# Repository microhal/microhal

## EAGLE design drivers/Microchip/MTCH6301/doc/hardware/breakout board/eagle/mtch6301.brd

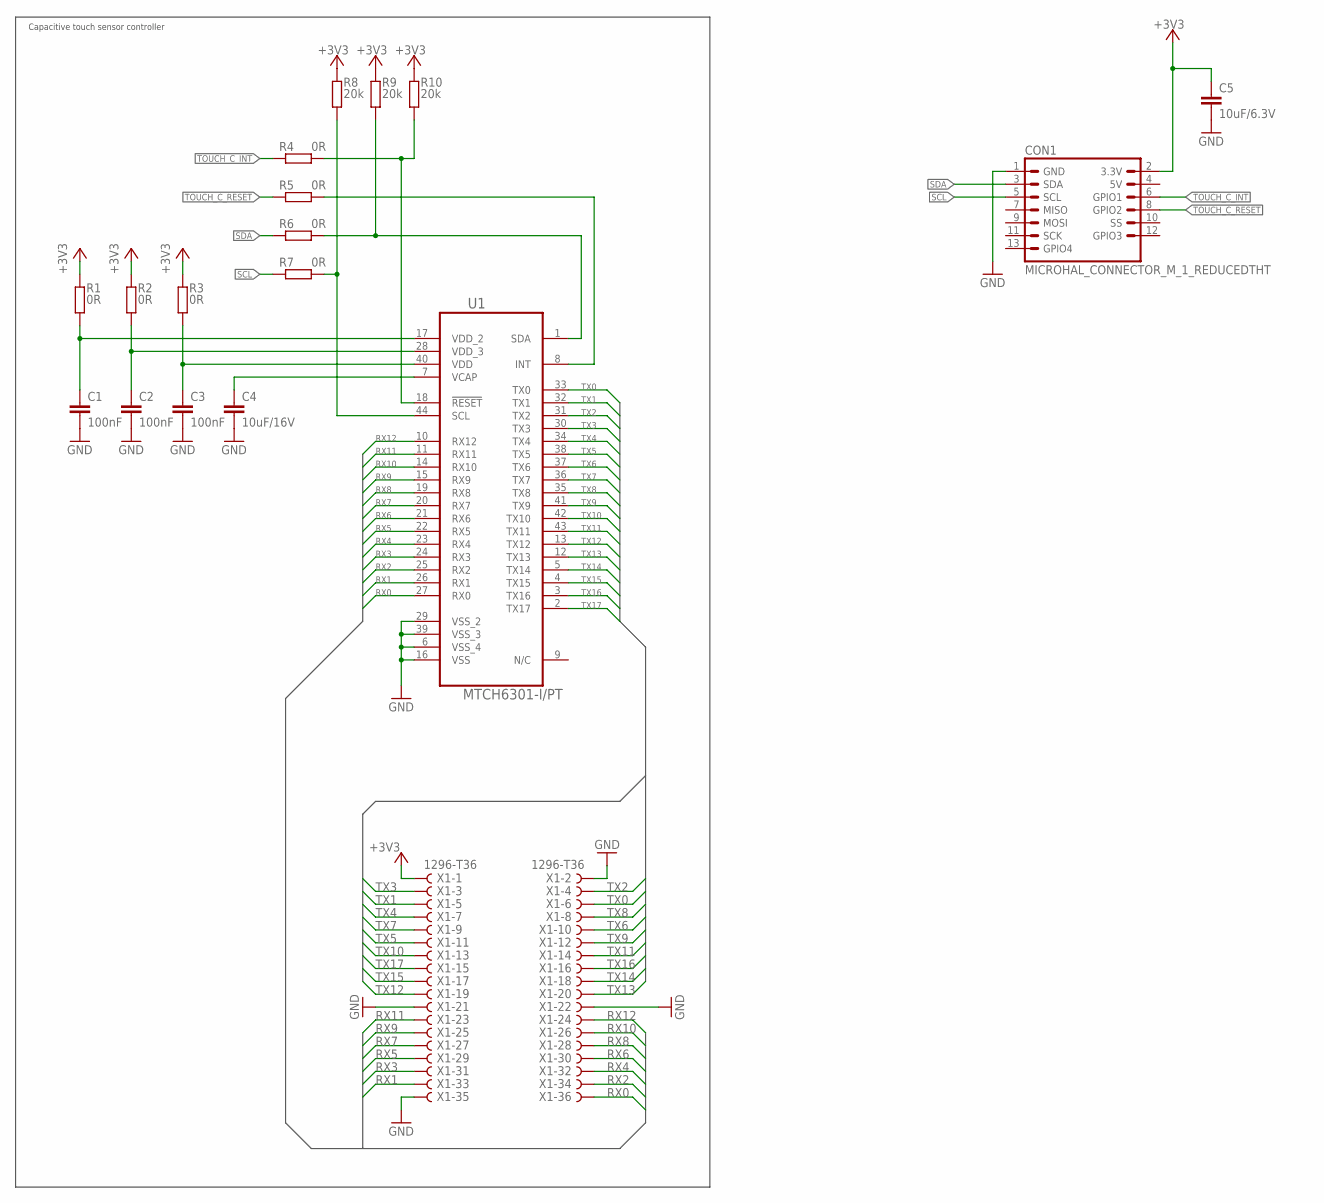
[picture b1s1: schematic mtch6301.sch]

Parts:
C1, C2, C3: 100nF; C0603K
C4: 10uF/16V; C1206K
C5: 10uF/6.3V; C0805K
CON1: MICROHAL_CONNECTOR_M_1_REDUCEDTHT; MA07-2
R1, R2, R3, R4, R5, R6, R7: 0R; R0603
R8, R9, R10: 20k; R0603
U1: MTCH6301-I/PT; TQFP80P1200X1200X120-44N
X1: 1296-T36; 1296-36

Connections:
+3V3: C5.1, CON1.2 (3.3V), R1.1, R2.1, R3.1, R8.1, R9.1, R10.1, X1.1
GND: C1.2, C2.2, C3.2, C4.2, C5.2, CON1.1 (GND), U1.6 (VSS_4), U1.16 (VSS), U1.29 (VSS_2), U1.39 (VSS_3), X1.2, X1.21, X1.22, X1.35
unnamed: C4.1, U1.7 (VCAP)
unnamed: C3.1, R3.2, U1.40 (VDD)
unnamed: C2.1, R2.2, U1.28 (VDD_3)
unnamed: C1.1, R1.2, U1.17 (VDD_2)
unnamed: R7.1, R8.2, U1.44 (SCL)
unnamed: R4.1, R10.2, U1.18 (!RESET)
unnamed: R6.1, R9.2, U1.1 (SDA)
unnamed: R5.1, U1.8 (INT)
RX0: U1.27 (RX0), X1.36
RX1: U1.26 (RX1), X1.33
RX2: U1.25 (RX2), X1.34
RX3: U1.24 (RX3), X1.31
RX4: U1.23 (RX4), X1.32
RX5: U1.22 (RX5), X1.29
RX6: U1.21 (RX6), X1.30
RX7: U1.20 (RX7), X1.27
RX8: U1.19 (RX8), X1.28
RX9: U1.15 (RX9), X1.25
RX10: U1.14 (RX10), X1.26
RX11: U1.11 (RX11), X1.23
RX12: U1.10 (RX12), X1.24
SCL: CON1.5 (SCL), R7.2
SDA: CON1.3 (SDA), R6.2
TOUCH_C_INT: CON1.6 (GPIO1), R4.2
TOUCH_C_RESET: CON1.8 (GPIO2), R5.2
TX0: U1.33 (TX0), X1.6
TX1: U1.32 (TX1), X1.5
TX2: U1.31 (TX2), X1.4
TX3: U1.30 (TX3), X1.3
TX4: U1.34 (TX4), X1.7
TX5: U1.38 (TX5), X1.11
TX6: U1.37 (TX6), X1.10
TX7: U1.36 (TX7), X1.9
TX8: U1.35 (TX8), X1.8
TX9: U1.41 (TX9), X1.12
TX10: U1.42 (TX10), X1.13
TX11: U1.43 (TX11), X1.14
TX12: U1.13 (TX12), X1.19
TX13: U1.12 (TX13), X1.20
TX14: U1.5 (TX14), X1.18
TX15: U1.4 (TX15), X1.17
TX16: U1.3 (TX16), X1.16
TX17: U1.2 (TX17), X1.15

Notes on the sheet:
Capacitive touch sensor controller

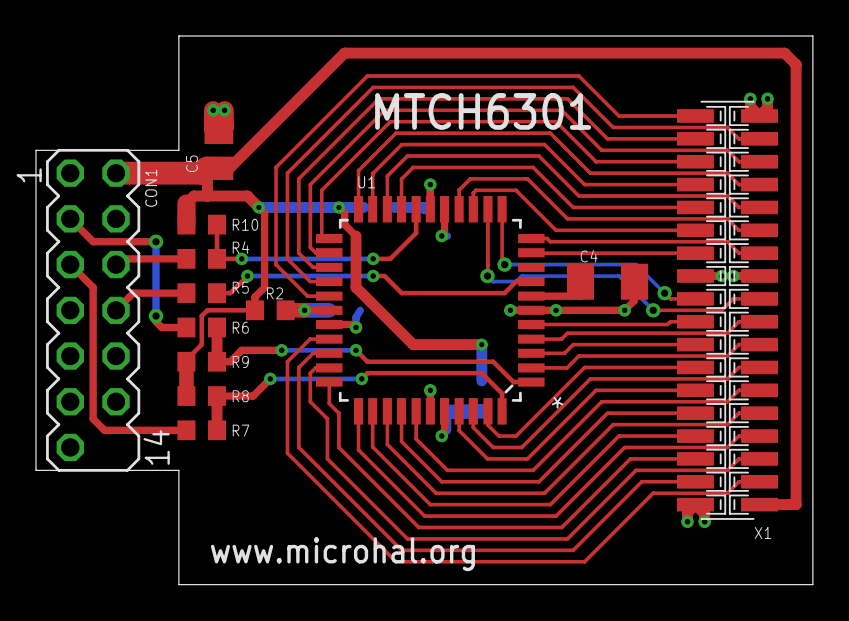
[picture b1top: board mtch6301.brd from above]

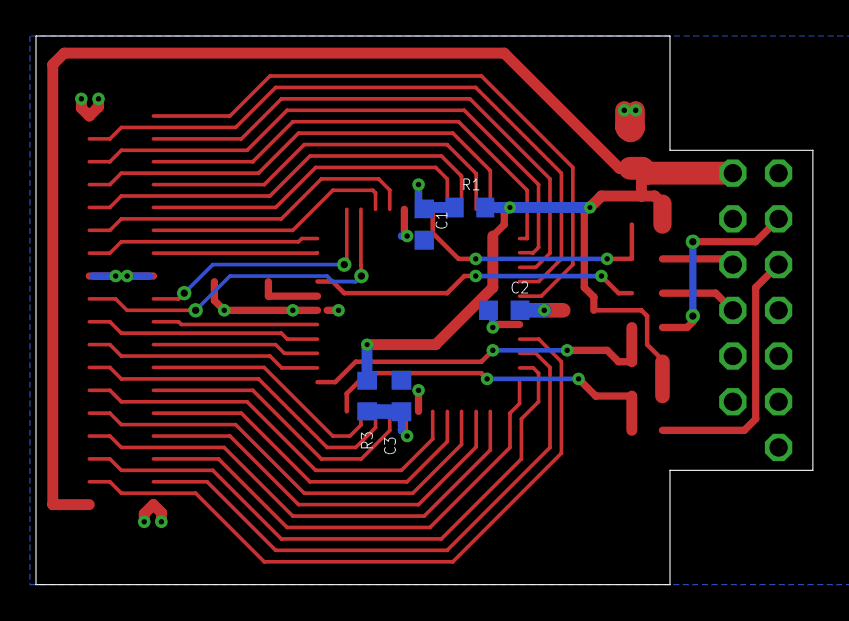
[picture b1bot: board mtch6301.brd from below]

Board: 2 copper layers, 43.2 x 30.5 mm, 18 parts (5 on the bottom side), 45 nets.

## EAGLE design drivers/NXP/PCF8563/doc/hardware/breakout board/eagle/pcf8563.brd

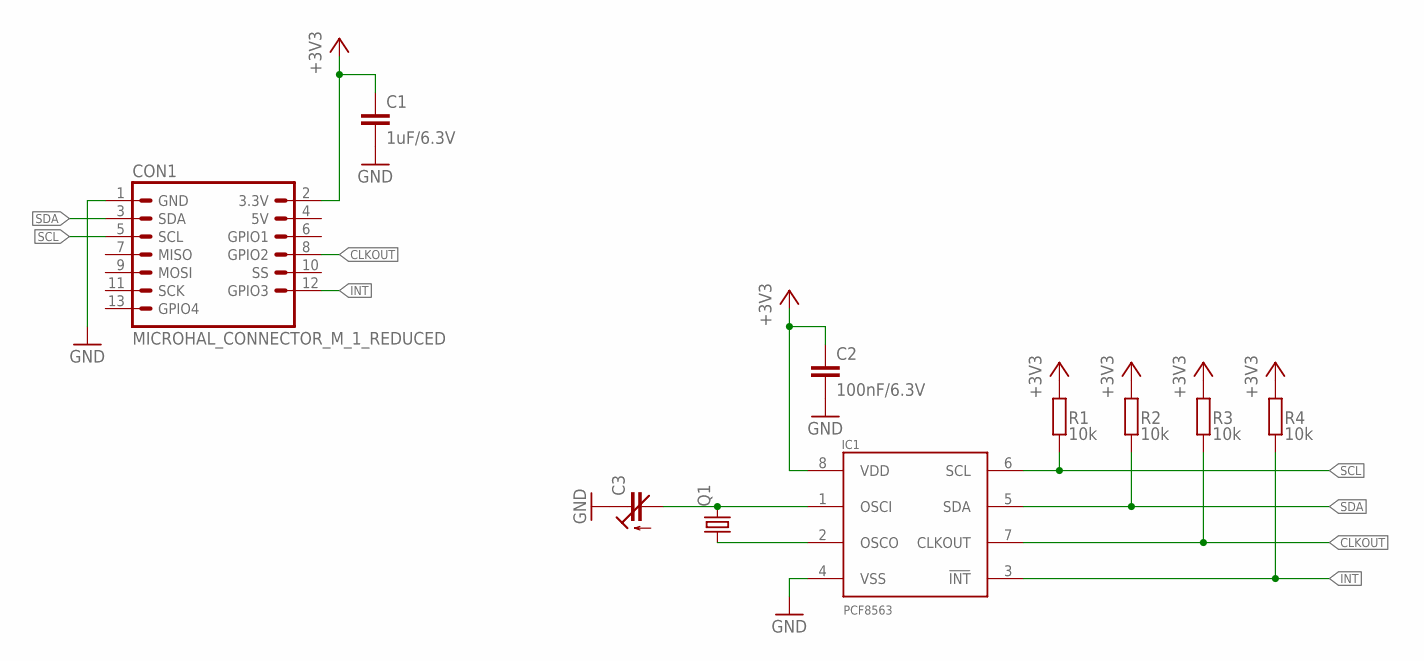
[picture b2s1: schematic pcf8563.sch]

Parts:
C1: 1uF/6.3V; C0805K
C2: 100nF/6.3V; C0603K
C3: C-TRIMMTZBX4; CTRIMTZBX4
CON1: MICROHAL_CONNECTOR_M_1_REDUCED; MICROHAL_CONNECTOR_M_1_REDUCED_EDGE
IC1: PCF8563; SO08
Q1: CRYSTALTC38H; TC38H
R1, R2, R3, R4: 10k; R0603

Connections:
+3V3: C1.1, C2.1, CON1.2 (3.3V), IC1.8 (VDD), R1.2, R2.2, R3.2, R4.2
CLKOUT: CON1.8 (GPIO2), IC1.7 (CLKOUT), R3.1
GND: C1.2, C2.2, C3.1 (E), CON1.1 (GND), IC1.4 (VSS)
INT: CON1.12 (GPIO3), IC1.3 (!INT), R4.1
unnamed: C3.2 (A), IC1.1 (OSCI), Q1.2
unnamed: IC1.2 (OSCO), Q1.1
SCL: CON1.5 (SCL), IC1.6 (SCL), R1.1
SDA: CON1.3 (SDA), IC1.5 (SDA), R2.1

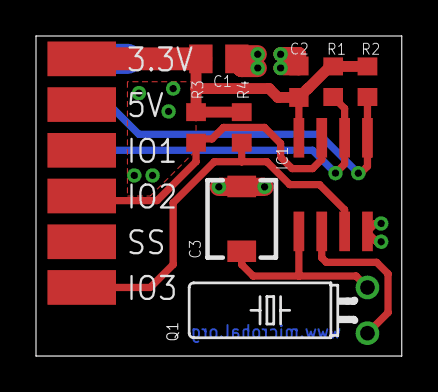
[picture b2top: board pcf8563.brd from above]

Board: 2 copper layers, 20.3 x 17.8 mm, 10 parts (0 on the bottom side), 8 nets.

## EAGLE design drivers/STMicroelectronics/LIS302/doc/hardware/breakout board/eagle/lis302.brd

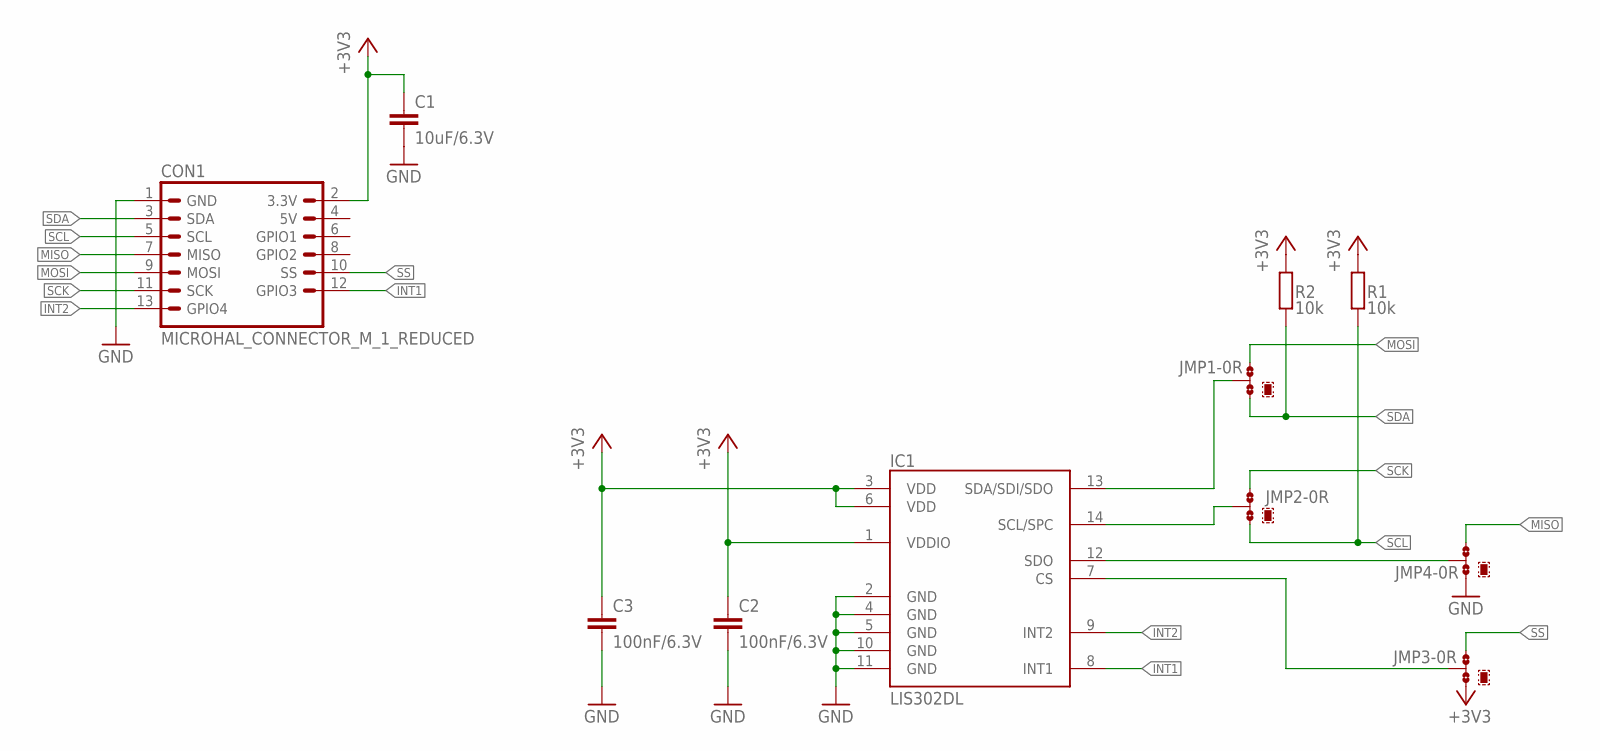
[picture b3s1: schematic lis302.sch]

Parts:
C1: 10uF/6.3V; C0805K
C2, C3: 100nF/6.3V; C0603K
CON1: MICROHAL_CONNECTOR_M_1_REDUCED; MICROHAL_CONNECTOR_M_1_REDUCED_EDGE
IC1: LIS302DL; LGA14
JMP1, JMP2, JMP3, JMP4: 0R-JUMPC; C0R-JMP
R1, R2: 10k; R0603

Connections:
+3V3: C1.1, C2.1, C3.1, CON1.2 (3.3V), IC1.1 (VDDIO), IC1.3 (VDD), IC1.6 (VDD), JMP3.1, R1.2, R2.2
GND: C1.2, C2.2, C3.2, CON1.1 (GND), IC1.2 (GND), IC1.4 (GND), IC1.5 (GND), IC1.10 (GND), IC1.11 (GND), JMP4.1
INT1: CON1.12 (GPIO3), IC1.8 (INT1)
INT2: CON1.13 (GPIO4), IC1.9 (INT2)
MISO: CON1.7 (MISO), JMP4.3
MOSI: CON1.9 (MOSI), JMP1.3
unnamed: IC1.13 (SDA/SDI/SDO), JMP1.2
unnamed: IC1.14 (SCL/SPC), JMP2.2
unnamed: IC1.12 (SDO), JMP4.2
unnamed: IC1.7 (CS), JMP3.2
SCK: CON1.11 (SCK), JMP2.3
SCL: CON1.5 (SCL), JMP2.1, R1.1
SDA: CON1.3 (SDA), JMP1.1, R2.1
SS: CON1.10 (SS), JMP3.3

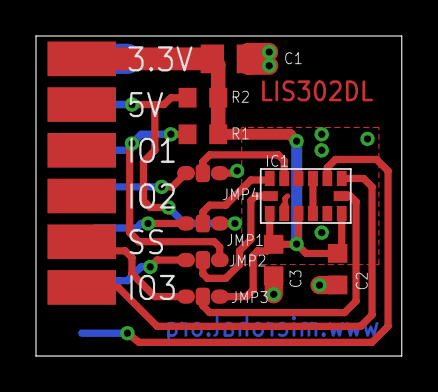
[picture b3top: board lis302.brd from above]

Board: 2 copper layers, 20.3 x 17.8 mm, 11 parts (0 on the bottom side), 14 nets.

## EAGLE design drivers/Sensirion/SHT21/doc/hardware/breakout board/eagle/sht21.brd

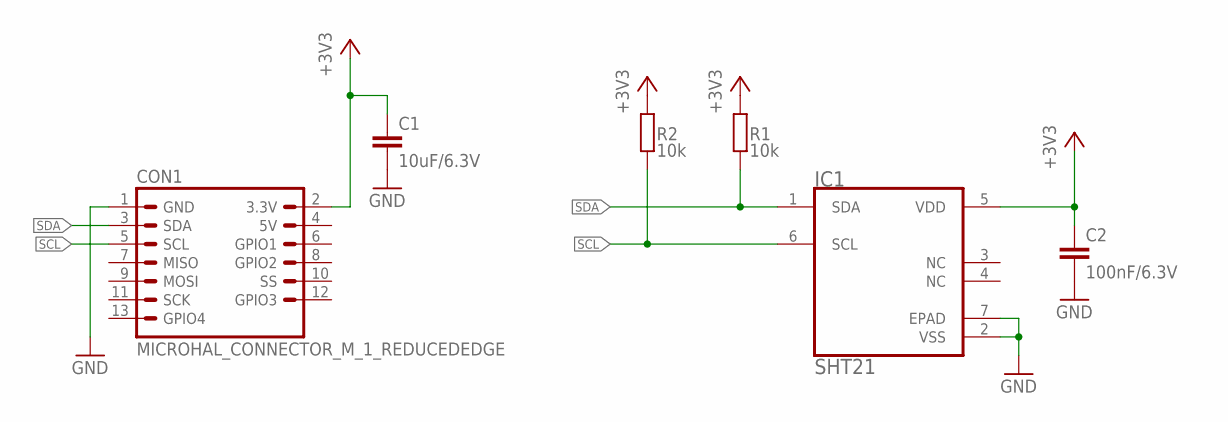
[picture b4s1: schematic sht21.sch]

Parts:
C1: 10uF/6.3V; C0603K
C2: 100nF/6.3V; C0603K
CON1: MICROHAL_CONNECTOR_M_1_REDUCEDEDGE; MICROHAL_CONNECTOR_M_1_REDUCED_EDGE
IC1: SHT21; DFN300X300X110-7N
R1, R2: 10k; R0603

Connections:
+3V3: C1.1, C2.1, CON1.2 (3.3V), IC1.5 (VDD), R1.2, R2.2
GND: C1.2, C2.2, CON1.1 (GND), IC1.2 (VSS), IC1.7 (EPAD)
SCL: CON1.5 (SCL), IC1.6 (SCL), R2.1
SDA: CON1.3 (SDA), IC1.1 (SDA), R1.1

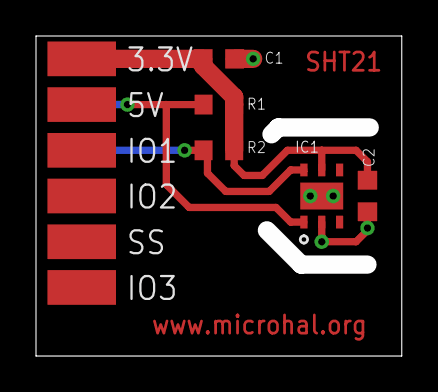
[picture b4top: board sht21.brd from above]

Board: 2 copper layers, 20.3 x 17.8 mm, 6 parts (0 on the bottom side), 4 nets.

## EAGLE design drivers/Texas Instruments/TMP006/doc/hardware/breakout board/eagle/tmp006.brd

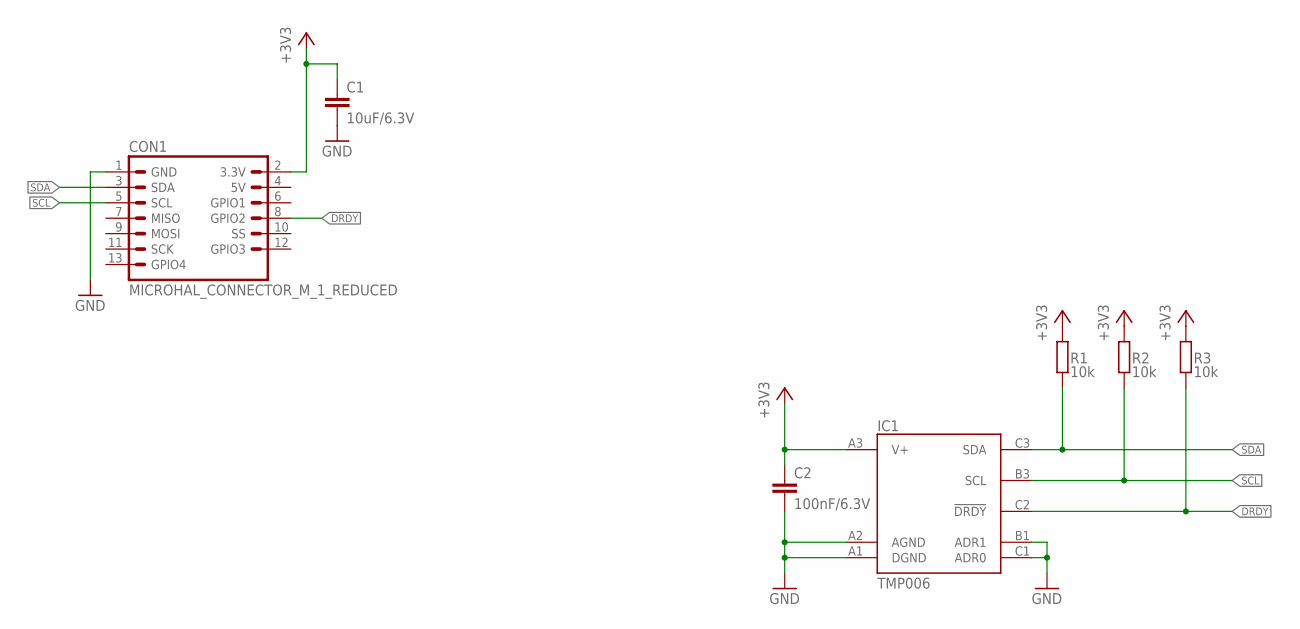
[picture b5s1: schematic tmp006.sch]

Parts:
C1: 10uF/6.3V; C0805K
C2: 100nF/6.3V; C0603K
CON1: MICROHAL_CONNECTOR_M_1_REDUCED; MICROHAL_CONNECTOR_M_1_REDUCED_EDGE
IC1: TMP006; DSBGA-8
R1, R2, R3: 10k; R0603

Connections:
+3V3: C1.1, C2.1, CON1.2 (3.3V), IC1.A3 (V+), R1.2, R2.2, R3.2
DRDY: CON1.8 (GPIO2), IC1.C2 (!DRDY), R3.1
GND: C1.2, C2.2, CON1.1 (GND), IC1.A1 (DGND), IC1.A2 (AGND), IC1.B1 (ADR1), IC1.C1 (ADR0)
SCL: CON1.5 (SCL), IC1.B3 (SCL), R2.1
SDA: CON1.3 (SDA), IC1.C3 (SDA), R1.1

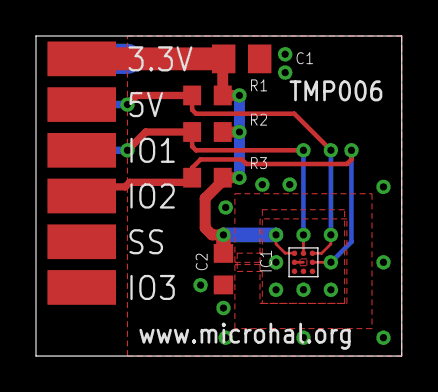
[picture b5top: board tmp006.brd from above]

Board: 2 copper layers, 20.3 x 17.8 mm, 7 parts (0 on the bottom side), 5 nets.

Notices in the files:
parts and their libraries:
pcf8563: Copyright (c) 2016, microHAL
All rights reserved.
